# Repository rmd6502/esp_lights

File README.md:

# esp_lights
Lights driven by ESP8266 and MQTT

# Setup
When first started, the lights will act as an access point, e.g. 'esp8266-lights-livingroom' The password will be whatever you set up in config.h

Select the SSID you want to connect to, enter the password and the IP of the MQTT server, and you should be good to go. You may need to manually reset or power cycle.

# Message
The message sent to the lights is to topic _/lightname/color_ and is a JSON payload, with retention set
_{ color: '#RRGGBB', brightness: 0-1 }_ . You can also leave the brightness at 1 and just change it with the color.

I believe there's also a React webapp included in this repo that will let you change the color of lights from a simple web app.

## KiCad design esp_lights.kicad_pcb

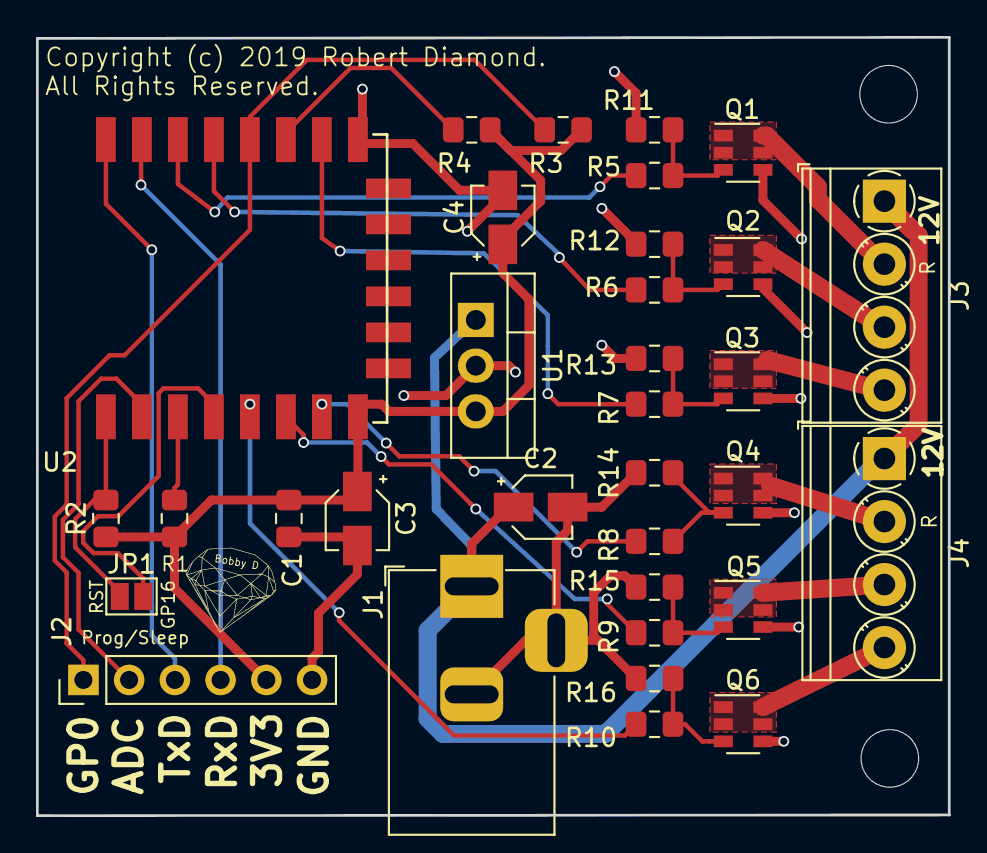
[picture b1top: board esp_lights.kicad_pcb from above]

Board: 2 copper layers, 50.7 x 43.2 mm, 33 parts (0 on the bottom side), 29 nets.

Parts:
C1: .1uf; C_0805_2012Metric_Pad1.15x1.40mm_HandSolder
C2: 1uf; CP_Elec_3x5.4
C3: 10uf; CP_Elec_3x5.4
C4: 2.2uf; CP_Elec_3x5.4
J1: Barrel_Jack; BarrelJack_Horizontal
J2: Conn_01x06_Female; PinHeader_1x06_P2.54mm_Vertical
J3, J4: Screw_Terminal_01x04; TerminalBlock_Phoenix_PT-1,5-4-3.5-H_1x04_P3.50mm_Horizontal
JP1: Jumper; SolderJumper-2_P1.3mm_Open_Pad1.0x1.5mm
Q1, Q2, Q3, Q4, Q5, Q6: PMN20EN; SOT-23-6
R1, R2, R3, R4, R11, R12, R13, R14, R15, R16: 10k; R_0805_2012Metric_Pad1.15x1.40mm_HandSolder
R5, R6, R7, R8, R9, R10: 100R; R_0805_2012Metric_Pad1.15x1.40mm_HandSolder
U1: LM7805_TO220; TO-220-3_Vertical
U2: ESP-12Q; ESP-12E_SMD

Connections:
+3V3: C1.1, C3.1, C4.1, J2.5, R1.1, R2.1, R3.1, R4.1, U1.3, U2.8
+12V: C2.1, J1.1, J3.1, J4.1, U1.1
ADC: J2.2, U2.2
Blue1: R7.1, U2.10
Blue2: R10.1, U2.5
GND: C1.2, C2.2, C3.2, C4.2, J1.2, J1.3, J2.6, Q1.4, Q2.4, Q3.4, Q4.4, Q5.4, Q6.4, R11.2, R12.2, R13.2, R14.2, R15.2, R16.2, U1.2, U2.9
GPIO0: J2.1, R3.2, U2.12
GPIO2: R4.2, U2.11
Green1: R6.1, U2.13
Green2: R9.1, U2.6
unnamed: J3.2, Q1.1, Q1.2, Q1.5, Q1.6
unnamed: J3.3, Q2.1, Q2.2, Q2.5, Q2.6
unnamed: J3.4, Q3.1, Q3.2, Q3.5, Q3.6
unnamed: J4.2, Q4.1, Q4.2, Q4.5, Q4.6
unnamed: J4.3, Q5.1, Q5.2, Q5.5, Q5.6
unnamed: J4.4, Q6.1, Q6.2, Q6.5, Q6.6
unnamed: JP1.1, R2.2, U2.1
unnamed: JP1.2, U2.4
unnamed: Q1.3, R5.2, R11.1
unnamed: Q2.3, R6.2, R12.1
unnamed: Q3.3, R7.2, R13.1
unnamed: Q4.3, R8.2, R14.1
unnamed: Q5.3, R9.2, R15.1
unnamed: Q6.3, R10.2, R16.1
unnamed: R1.2, U2.3
Red1: R5.1, U2.14
Red2: R8.1, U2.7
RxD: J2.4, U2.15
TxD: J2.3, U2.16

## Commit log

2019-10-06 initial copy back to git
2019-10-06 add more files
2019-10-08 add firmware
2023-01-23 add mqtt control
2023-03-15 Bump webpack from 5.75.0 to 5.76.1 in /mqtt-color-control
    Bumps [webpack](https://github.com/webpack/webpack) from 5.75.0 to 5.76.1.
    - [Release notes](https://github.com/webpack/webpack/releases)
    - [Commits](https://github.com/webpack/webpack/compare/v5.75.0...v5.76.1)
    ---
    updated-dependencies:
    - dependency-name: webpack

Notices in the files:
esp_lights.kicad_pcb:
Copyright (c) 2019 Robert Diamond.
All Rights Reserved.
